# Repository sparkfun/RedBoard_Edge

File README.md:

SparkFun RedBoard Edge
========================================

[*SparkFun RedBoard Edge (DEV-14525)*](https://www.sparkfun.com/products/14525)

The RedBoard Edge is a RedBoard that's been rebuilt around the idea that projects are eventually put into an enclosure to help clean up their look.

Repository Contents
-------------------

* **/Hardware** - Eagle design files (.brd, .sch)
* **/Production** - Production panel files.

Documentation
--------------
* **[Hookup Guide](https://learn.sparkfun.com/tutorials/redboard-edge-hookup-guide)** - Basic hookup guide for the RedBoard Edge.

Product Versions
----------------
* [DEV-14525](https://www.sparkfun.com/products/14525)- SparkFun red version
* *[SPX-14471 (RETIRED)](https://www.sparkfun.com/products/retired/14471)- SparkX version*

License Information
-------------------

This product is _**open source**_! 

Please review the LICENSE.md file for license information. 

If you have any questions or concerns on licensing, please contact techsupport@sparkfun.com.

Distributed as-is; no warranty is given.

- Your friends at SparkFun.

_<COLLABORATION CREDIT>_

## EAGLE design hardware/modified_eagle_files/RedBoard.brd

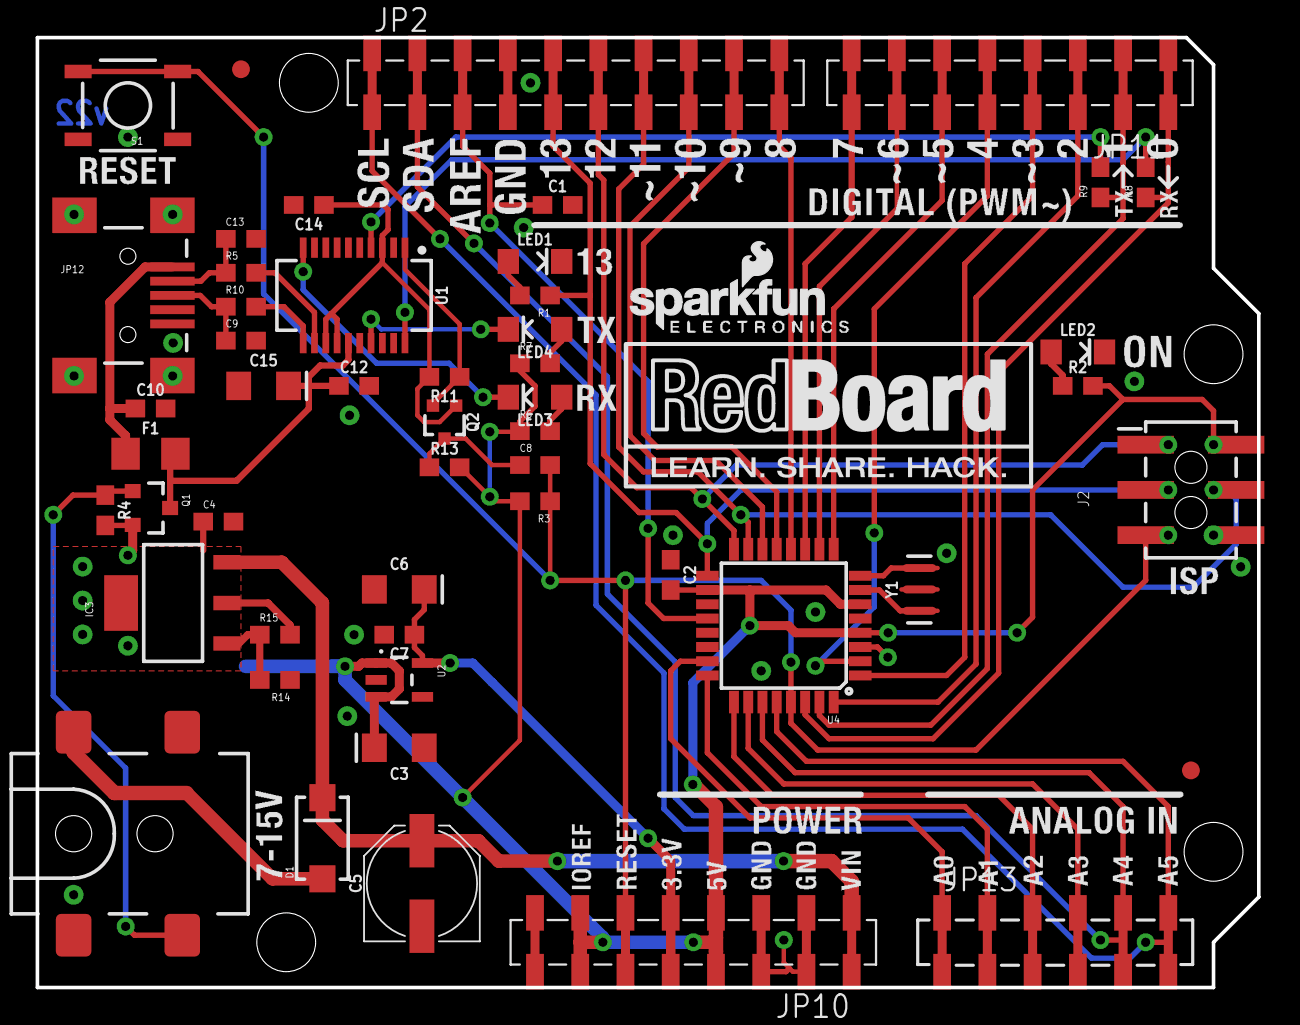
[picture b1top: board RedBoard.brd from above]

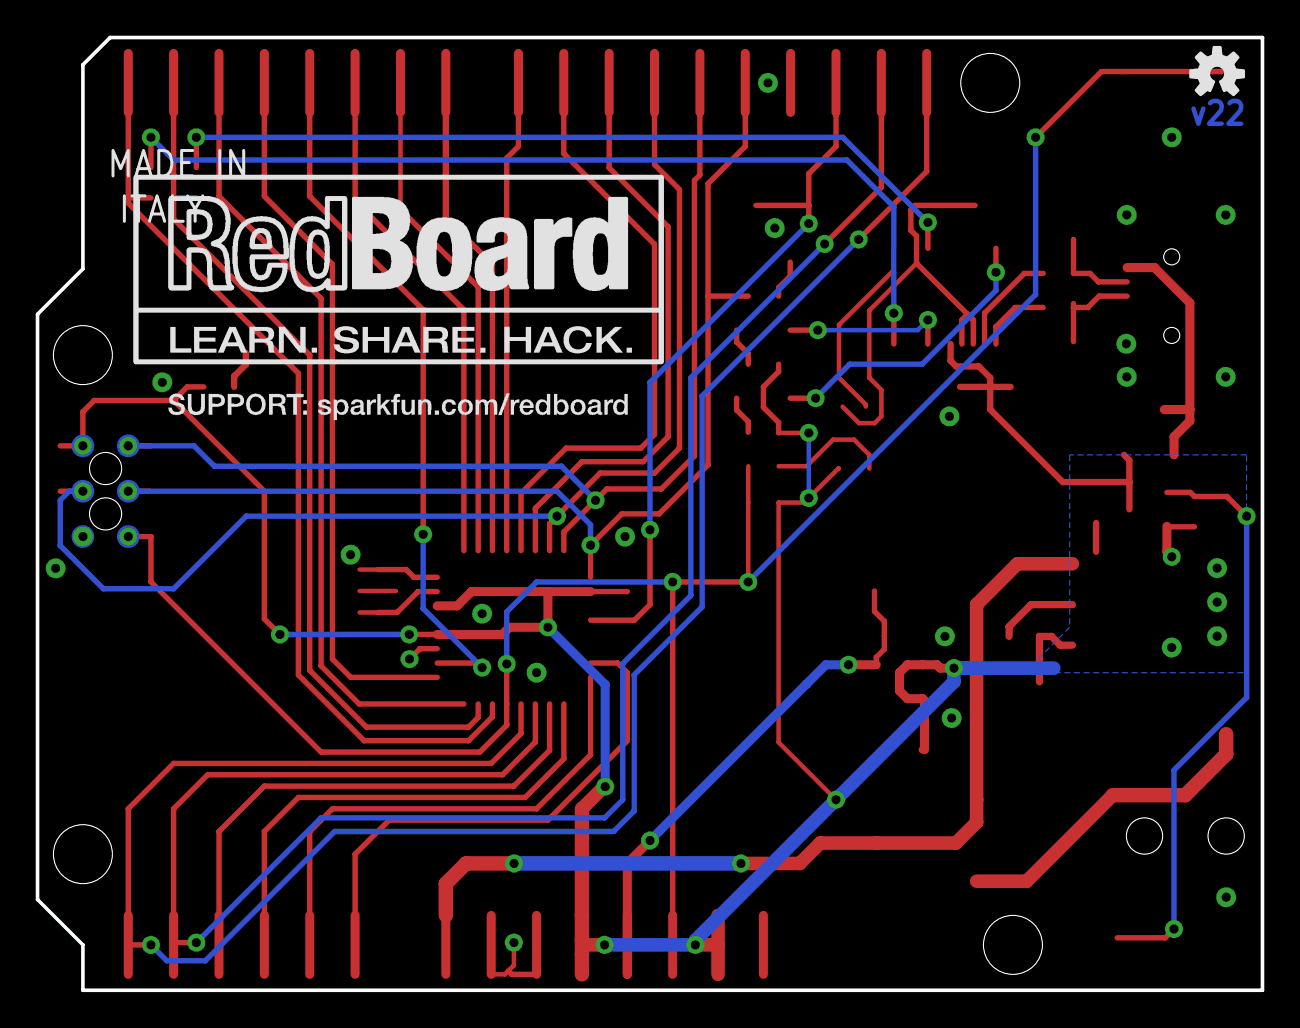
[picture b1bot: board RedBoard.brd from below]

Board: 2 copper layers, 68.6 x 53.3 mm, 88 parts (7 on the bottom side), 48 nets.

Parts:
C1, C2, C4, C8, C10, C12, C14: 0.1uF; 0603
C3, C6, C15: 10uF; EIA3216
C5: 47uF; PANASONIC_D
C7: 1.0uF; 0603
C9, C13: 47pF; 0603
D1: MBRA140; SMA-DIODE
F1: 6V/0.5A; 1206
FRAME2: FRAME-LETTER; CREATIVE_COMMONS
IC3: LM1117; SOT223-ALT1
J2: ICSP; 2X3_SMT_POSTS
J3: POWER_JACKSUPER_BOMB_DIGITY; POWER_JACK_SMD_OVERPASTE_SUPER_BOMB_DIGITY
JP1: SFE_LOGO_NAME.1_INCH; SFE_LOGO_NAME_.1
JP2: M10SMD_COMBO; 1X10_SMD_COMBINED
JP3, JP4, JP5, JP6: STAND-OFF
JP7: SFE_LOGO_FLAME.1_INCH; SFE_LOGO_FLAME_.1
JP8, JP9: FIDUCIAL1X2; FIDUCIAL-1X2
JP10: JP10; 1X08_SMD_COMBINED
JP11: IOL; 1X08_SMD_COMBINED
JP12: USB-MINIB-5PIN; USB-MINIB
JP13: AD; 1X06_SMD_STRAIGHT_COMBO
LED1: Blue; LED-1206
LED2: Green; LED-1206
LED3: Red; LED-1206
LED4: Yellow; LED-1206
Q1: 1A/60V/500mΩ; SOT23-3
Q2: 2N7002PW; SOT323
R1, R6, R7, R8, R9: 1k; 0603
R2: 4.7k; 0603
R3, R4, R11, R13: 10k; 0603
R5, R10: 27; 0603
R14: 715; 0603
R15: 240; 0603
S1: RESET; TACTILE-SWITCH-SMD
TP1, TP2, TP3, TP4, TP5, TP6: TP-3x5; PAD.03X.05
U1: FT231XS; SSOP20_L
U2: MIC5205; SOT23-5
U4: ATMEGA328P_TQFP; TQFP32-08
U$16: OSHW-LOGOS; OSHW-LOGO-S
VP_0, VP_1, VP_2, VP_3, VP_4, VP_5, VP_6, VP_7, VP_8, VP_9, VP_10, VP_11, VP_12, VP_13, VP_14, VP_15, VP_16, VP_17, VP_18, VP_19, VP_20, VP_21, VP_22: VPDEV0; VPAC0
Y1: 16MHz; RESONATOR-SMD-3.2X1.3

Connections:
3.3V: C6.+, C7.1, JP10.5A, JP10.5B, U2.5
3.3V_F: C14.1, Q2.1, R11.2, U1.3, U1.13, U1.14
5V: C2.2, C3.+, C4.1, IC3.2, IC3.4, J2.2, JP10.4A, JP10.4B, JP10.7A, JP10.7B, Q1.2, R2.2, R3.2, R4.2, R6.1, R7.1, R13.2, R15.2, TP1.P$1, U2.1, U2.3, U4.4, U4.6, U4.18, VP_0.VP, VP_1.VP, VP_2.VP, VP_3.VP
AD0: JP13.1A, JP13.1B, U4.23
AD1: JP13.2A, JP13.2B, U4.24
AD2: JP13.3A, JP13.3B, U4.25
AD3: JP13.4A, JP13.4B, U4.26
AD4/SDA: JP2.2A, JP2.2B, JP13.5A, JP13.5B, U4.27
AD5/SCL: JP2.1A, JP2.1B, JP13.6A, JP13.6B, U4.28
AREF: C1.1, JP2.3A, JP2.3B, U4.20
D+: C9.1, JP12.D+, R10.1
D-: C13.1, JP12.D-, R5.1
DTR: C8.1, Q2.3, R13.1
FTDI_DTR: Q2.2, R11.1, U1.1
GND: C1.2, C2.1, C3.-, C4.2, C5.-, C6.-, C7.2, C9.2, C10.2, C12.2, C13.2, C14.2, C15.-, J2.6, J3.GND, JP2.4A, JP2.4B, JP10.2A, JP10.2B, JP10.3A, JP10.3B, JP12.GND, JP12.MTN1, JP12.MTN2, JP12.MTN3, JP12.MTN4, LED1.C, LED2.C, R14.1, S1.1, S1.2, TP3.P$1, U1.6, U1.16, U2.2, U4.3, U4.5, U4.21, VP_4.VP, VP_5.VP, VP_6.VP, VP_7.VP, VP_8.VP, VP_9.VP, VP_10.VP, VP_11.VP, VP_12.VP, VP_13.VP, VP_14.VP, VP_15.VP, VP_16.VP, VP_17.VP, VP_18.VP, VP_19.VP, VP_20.VP, VP_21.VP, VP_22.VP, Y1.2
INSERT: J3.P$4, Q1.1, R4.1
IO2: JP11.3A, JP11.3B, U4.32
IO3: JP11.4A, JP11.4B, U4.1
IO4: JP11.5A, JP11.5B, U4.2
IO5: JP11.6A, JP11.6B, U4.9
IO6: JP11.7A, JP11.7B, U4.10
IO7: JP11.8A, JP11.8B, U4.11
IO8: JP2.10A, JP2.10B, U4.12
IO9: JP2.9A, JP2.9B, U4.13
MISO: J2.1, JP2.6A, JP2.6B, TP4.P$1, U4.16
MOSI: J2.4, JP2.7A, JP2.7B, TP2.P$1, U4.15
unnamed: LED1.A, R1.2
unnamed: LED2.A, R2.1
unnamed: U4.7, Y1.1
unnamed: U4.8, Y1.3
unnamed: R5.2, U1.12
unnamed: R10.2, U1.11
unnamed: LED3.A, R6.2
unnamed: LED4.A, R7.2
unnamed: IC3.1, R14.2, R15.1
PWRIN: D1.A, J3.VIN0
RESET: C8.2, J2.5, JP10.6A, JP10.6B, R3.1, S1.3, S1.4, TP6.P$1, U4.29
RX-I: JP11.1A, JP11.1B, R8.1, U4.30
RXD: R9.2, U1.4
RXLED: LED4.C, U1.17
SCK: J2.3, JP2.5A, JP2.5B, R1.1, TP5.P$1, U4.17
SS: JP2.8A, JP2.8B, U4.14
TX-O: JP11.2A, JP11.2B, R9.1, U4.31
TXD: R8.2, U1.20
TXLED: LED3.C, U1.10
USBVCC: C12.1, C15.+, F1.2, Q1.3, U1.15
VIN: C5.+, D1.C, IC3.3, JP10.1A, JP10.1B
VUSB: C10.1, F1.1, JP12.VBUS

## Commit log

2017-10-26 conversion to Reds, all parts now point to KiCad library in directory C:/Github
2017-11-02 Conversion to Reds
2017-11-03 Post Design review changes
2017-11-03 Checklist changes
2017-11-03 forgot to save before commit
2017-11-07 QC Double Check Issues
2017-11-09 Post double double check changes
2017-11-14 fixed gerbers
2017-12-18 updated 12mhz crystal
2018-01-02 cleaned repo
2018-01-03 post design review changes, added switch
2018-01-04 added CC 4.0
2018-01-05 Post double check changes
2018-01-19 updated toggle switch
2018-02-02 fixed xtal
2018-02-07 removed circle
2018-02-08 Fixed broken kicad file
2018-02-09 QC Checklist changes
2018-02-13 panel
2018-05-31 cleaning repo
2018-05-31 fixed typo
2018-06-01 attampting to remove extra hardware files
2018-06-01 fixing repo

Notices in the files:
parts and their libraries:
SparkFun-Aesthetics: Licensing: CC v3.0 Share-Alike You are welcome to use this library for commercial purposes.
SparkFun-Aesthetics: Released under the Creative Commons Attribution Share-Alike 4.0 License
SparkFun-Aesthetics: https://creativecommons.org/licenses/by-sa/4.0
